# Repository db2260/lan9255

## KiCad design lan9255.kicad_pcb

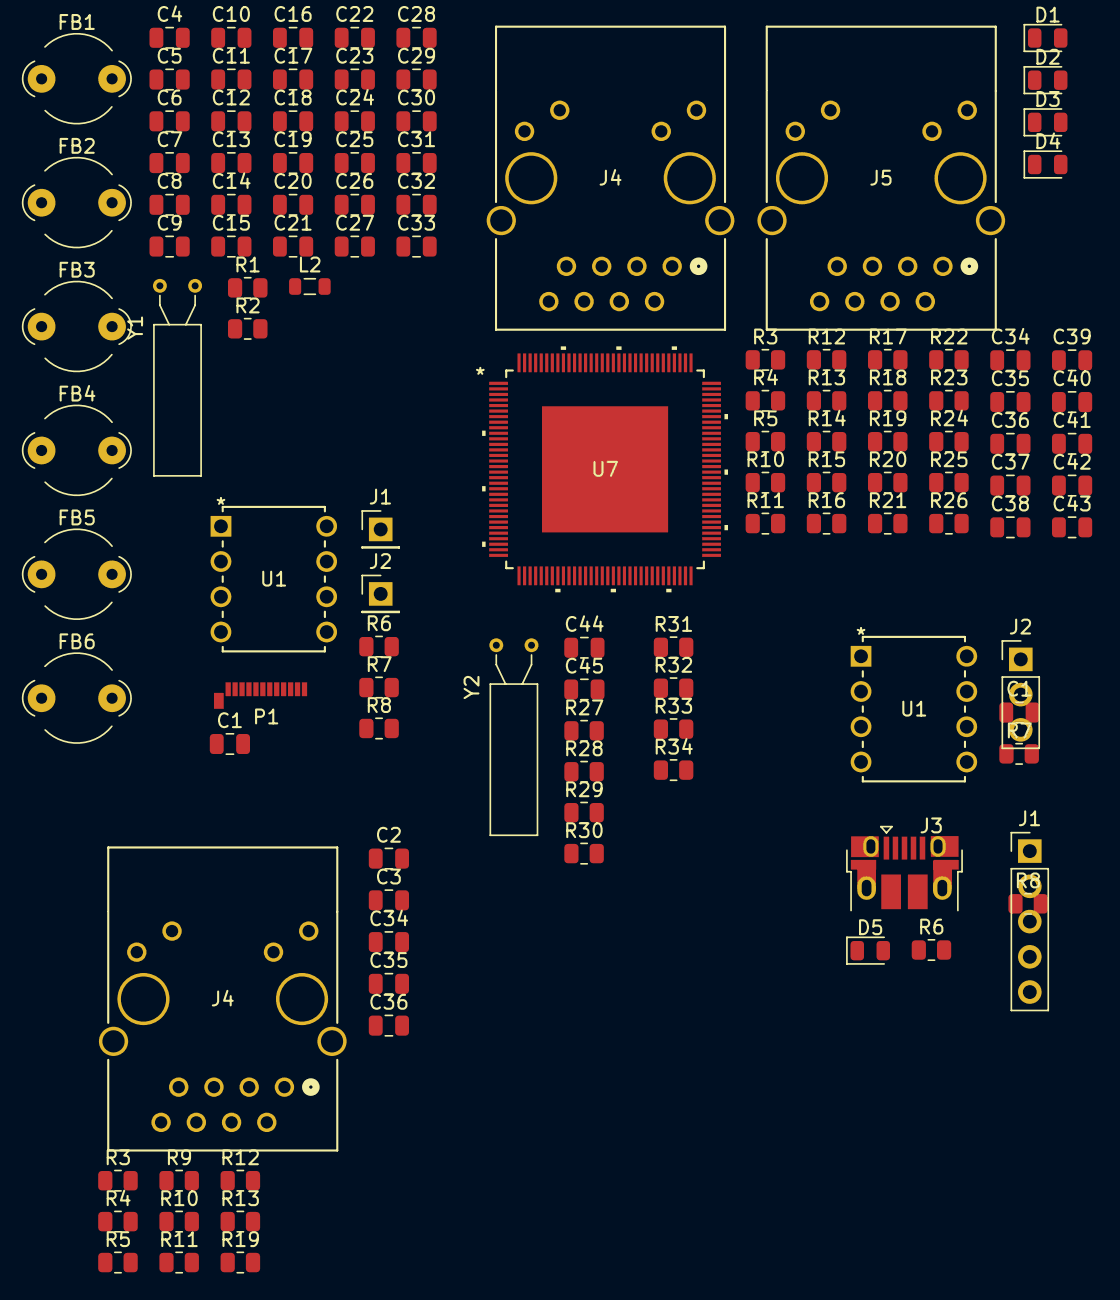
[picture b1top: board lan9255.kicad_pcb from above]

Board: 2 copper layers, 120 parts (0 on the bottom side), 69 nets, no tracks yet.

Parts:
C1, C1#2, C7, C8, C10, C11, C12, C13, C14, C15, C16, C17, C18, C19, C20, C21, C23, C27: 0.1u; C_0805_2012Metric
C2, C3, C34, C34#2, C35, C35#2, C36, C37, C39, C40, C41, C42, C44, C45: 10p; C_0805_2012Metric
C4, C5, C6, C28, C29, C30, C31: 10u; C_0805_2012Metric
C9, C24: 1u; C_0805_2012Metric
C22: 4.7u; C_0805_2012Metric
C25: 100n; C_0805_2012Metric
C26: 470p; C_0805_2012Metric
C32, C33: 5p; C_0805_2012Metric
C36#2, C38, C43: 0.022u; C_0805_2012Metric
D1, D2, D3: D; D_0805_2012Metric
D4, D5: LED; LED_0805_2012Metric
FB1, FB2, FB3, FB4, FB5: 220R; LairdTech_28C0236-0JW-10
FB6: 33R; LairdTech_28C0236-0JW-10
J1: Conn_01x05; PinHeader_1x05_P2.54mm_Vertical
J1#2: Conn_01x05; PinHeader_1x01_P2.54mm_Vertical
J2: Conn_01x03; PinHeader_1x03_P2.54mm_Vertical
J2#2: Conn_01x03; PinHeader_1x01_P2.54mm_Vertical
J3: USB_B_Micro; USB_Micro-B_Amphenol_10103594-0001LF_Horizontal
J4, J4#2, J5: J0011D01BNL; CONN12_011D01BNL_PUL
L2: 10u; L_0805_2012Metric
P1: USB_C_Plug_USB2.0; USB_C_Plug_Molex_105444
R1, R2, R7, R7#2, R8, R8#2, R24, R25, R31, R32, R33: 10k; R_0805_2012Metric
R3, R3#2, R4, R4#2, R5, R5#2, R10, R10#2, R14, R15, R16, R17: 49.9; R_0805_2012Metric
R6: 2.2k; R_0805_2012Metric
R6#2: 5.1k; R_0805_2012Metric
R9, R12, R12#2, R13, R13#2, R19, R19#2, R20: 330; R_0805_2012Metric
R11, R11#2, R18: 0; R_0805_2012Metric
R21, R22, R23: 332; R_0805_2012Metric
R26: 1k; R_0805_2012Metric
R27, R28, R29: 33; R_0805_2012Metric
R30: 22; R_0805_2012Metric
R34: 12.1k; R_0805_2012Metric
U1, U1#2: 24FC512-I/P; PDIP8_300MC_MCH
U7: LAN9255; 128-TQFP_9.0EPAD_MCH
Y1: 25MHz; Crystal_AT310_D3.0mm_L10.0mm_Horizontal
Y2: 32.768kHz; Crystal_AT310_D3.0mm_L10.0mm_Horizontal

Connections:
+3V3: C1.1, C1#2.1, C4.1, C5.1, C6.1, C7.1, C8.1, C9.1, C10.1, C11.1, C12.1, C13.1, C14.1, C16.1, C19.1, C21.1, C30.1, FB1.2, FB2.1, FB3.1, FB4.2, R1.1, R2.1, R8.1, R8#2.1, R24.1, R25.1, R32.1, R33.1, U1.8 (VCC), U1#2.8 (VCC), U7.7 (VDD33), U7.29 (VDDIO_J), U7.37 (VDDIOB), U7.45 (VDDIO_J), U7.60 (VDDIO_J), U7.65 (VDDIO_S), U7.74 (VDDIO_J), U7.94 (VDDIO_J), U7.97 (VDDIO_S), U7.117 (VDDIO_S)
/Microcontroller/XIN32: C45.2, U7.3 (PA00), Y2.1
/Microcontroller/XOUT32: C44.1, U7.5 (PA01), Y2.2
/MiscSignals/SCL: J2#2.1, U1#2.6 (SCL)
CLK25: FB6.1, R30.2
GND: C1.2, C1#2.2, C2.2, C3.2, C4.2, C5.2, C6.2, C7.2, C8.2, C9.2, C10.2, C11.2, C12.2, C13.2, C14.2, C15.2, C16.2, C17.2, C18.2, C19.2, C20.2, C21.2, C22.2, C23.2, C24.2, C25.2, C26.2, C27.2, C28.2, C29.2, C30.2, C31.2, C32.2, C33.2, C34.2, C34#2.2, C35.2, C35#2.2, C36.2, C36#2.2, C37.2, C38.2, C39.2, C40.2, C41.2, C42.2, C43.2, C44.2, C45.1, D4.1 (K), D5.1 (K), J1.5, J2.3, J3.5 (GND), J3.6 (Shield), J4.8, J4#2.8, J5.8, P1.A1 (GND), P1.A12 (GND), P1.B1 (GND), P1.B12 (GND), P1.S1 (SHIELD), R6#2.2, R7.2, R7#2.2, R9.2, R12.2, R12#2.2, R13.2, R13#2.2, R19.2, R19#2.2, R20.2, R31.1, R34.2, U1.1 (A0), U1.2 (A1), U1.3 (A2), U1.4 (VSS), U1#2.1 (A0), U1#2.2 (A1), U1#2.3 (A2), U1#2.4 (VSS), U7.6 (OSCVSS)
LINK0: J1.3, J4.9, J4#2.9, R23.1, U7.95 (LINKACTLED0/TDO/CHIP_MODE0/LEDPOL0)
LINK1: J1.4, J5.9, R22.1, U7.90 (LINKACTLED1/TDI/CHIP_MODE1/LEDPOL1)
unnamed: C36#2.1, J4#2.4, J4#2.5, R11#2.2
unnamed: C38.1, J4.4, J4.5, R11.2
unnamed: C43.1, J5.4, J5.5, R18.2
unnamed: D1.1 (K), R21.2
unnamed: D2.1 (K), R22.2
unnamed: D3.1 (K), R23.2
unnamed: D4.2 (A), R26.1
unnamed: D5.2 (A), R6.2
unnamed: J4.10, J4#2.10, R12.1, R12#2.1
unnamed: J4.11, J4#2.11, R13.1, R13#2.1
unnamed: J5.10, R9.1, R19.1
unnamed: J5.11, R19#2.1, R20.1
unnamed: P1.A5 (CC), R6#2.1
unnamed: R7.1, R7#2.1, U1.7 (WP), U1#2.7 (WP)
unnamed: R33.2, U7.88 (IRQ/LATCH1)
unnamed: R34.1, U7.111 (RBIAS)
unnamed: R31.2, R32.2, U7.81 (TESTMODE)
unnamed: C27.1, U7.15 (GNDANA)
unnamed: R1.2, U7.13 (REG_EN)
unnamed: C29.1, FB5.1, U7.110 (VDD12TX1), U7.113 (VDD12TX2)
unnamed: C23.1, FB3.2, U7.112 (VDD33BIAS)
unnamed: C28.1, FB4.1, U7.16 (VDDANA)
unnamed: L2.2, U7.114 (VSW)
unnamed: FB6.2, U7.14 (CLK_25/CLK_25_EN/XTAL_MODE)
unnamed: C32.1, U7.128 (OSCI), Y1.2
unnamed: C33.1, U7.1 (OSCO), Y1.1
unnamed: R2.2, U7.21 (RST#), U7.108 (RESETN_E53)
unnamed: R26.2, U7.17 (ERRLED/PME/100FD_B/LEDPOL4)
unnamed: R21.1, U7.89 (RUNLED/STATE_RUNLED/E2PSIZE/EE_EMUL0/LE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)
unnamed: C35#2.1, C37.1, J4.6, J4#2.6, R10.2, R10#2.2, U7.105 (RXNA)
unnamed: C39.1, J5.1, R14.2, U7.116 (RXNB)
unnamed: C34.1, C36.1, J4.3, J4#2.3, R5.2, R5#2.2, U7.106 (RXPA)
unnamed: C41.1, J5.3, R16.2, U7.115 (RXPB)
unnamed: C3.1, C35.1, J4.2, J4#2.2, R4.2, R4#2.2, U7.103 (TXNA)
unnamed: C40.1, J5.2, R15.2, U7.119 (TXNB)
unnamed: C2.1, C34#2.1, J4.1, J4#2.1, R3.2, R3#2.2, U7.104 (TXPA)
unnamed: C42.1, J5.6, R17.2, U7.118 (TXPB)
unnamed: R27.1, U7.68 (PA17)
unnamed: R28.2, U7.69 (PA18)
unnamed: R29.2, U7.73 (PA19)
unnamed: R30.1, U7.98 (PB22)
QSPI_CLK: U7.40 (PB10), U7.41 (D9/AD9/LATCH_IN/SCK)
QSPI_CSn: U7.42 (PB11), U7.101 (D5/AD5/OUTVALID/SCS#)
QSPI_SIO0: U7.33 (PA08), U7.38 (D0/AD0/WD_STATE/SI/SIO0)
QSPI_SIO1: U7.26 (D1/AD1/EOF/SO/SIO1), U7.34 (PA09)
QSPI_SIO2: U7.24 (D2/AD2/SOF/SIO2/EE_EMUL_SPI0), U7.35 (PA10)
QSPI_SIO3: U7.36 (PA11), U7.71 (D3/AD3/WE_TRIG/SIO3/EE_EMUL_SPI1)
SCL: J2.1, U1.6 (SCL)
SDA: J2.2, U1.5 (SDA)
SYNC0: U7.70 (SYNC0/LATCH0/PME), U7.77 (PB16)
SYNC1: U7.39 (SYNC1/LATCH1/PME), U7.79 (PB17)
TCK: J1.1, J1#2.1, R8.2, R8#2.2, R25.2, U7.83 (EESCL/TCK/EE_EMUL2)
TMS: J1.2, R24.2, U7.82 (EESDA/TMS/EE_EMUL1)
USB0_N: J3.2 (D-), P1.A7 (D-), U7.93 (PA24)
USB0_P: J3.3 (D+), U7.96 (PA25)
VBUS: J3.1 (VBUS), P1.A4 (VBUS), P1.A9 (VBUS), P1.B4 (VBUS), P1.B9 (VBUS), R6.1
VDD33: D1.2 (A), D2.2 (A), D3.2 (A)
VDD33TXRX1: C15.1, FB1.1, R3.1, R3#2.1, R4.1, R4#2.1, R5.1, R5#2.1, R10.1, R10#2.1, R11.1, R11#2.1, U7.102 (VDD33TXRX1)
VDD33TXRX2: C18.1, FB2.2, R14.1, R15.1, R16.1, R17.1, R18.1, U7.124 (VDD33TXRX2)
VDDCORE: C22.1, C25.1, L2.1, U7.109 (VDDCORE)
VDDCR: C17.1, C20.1, C24.1, C26.1, C31.1, FB5.2, U7.12 (VDDCR), U7.52 (VDDCR), U7.76 (VDDCR)

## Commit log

2024-09-27 LAN9255
